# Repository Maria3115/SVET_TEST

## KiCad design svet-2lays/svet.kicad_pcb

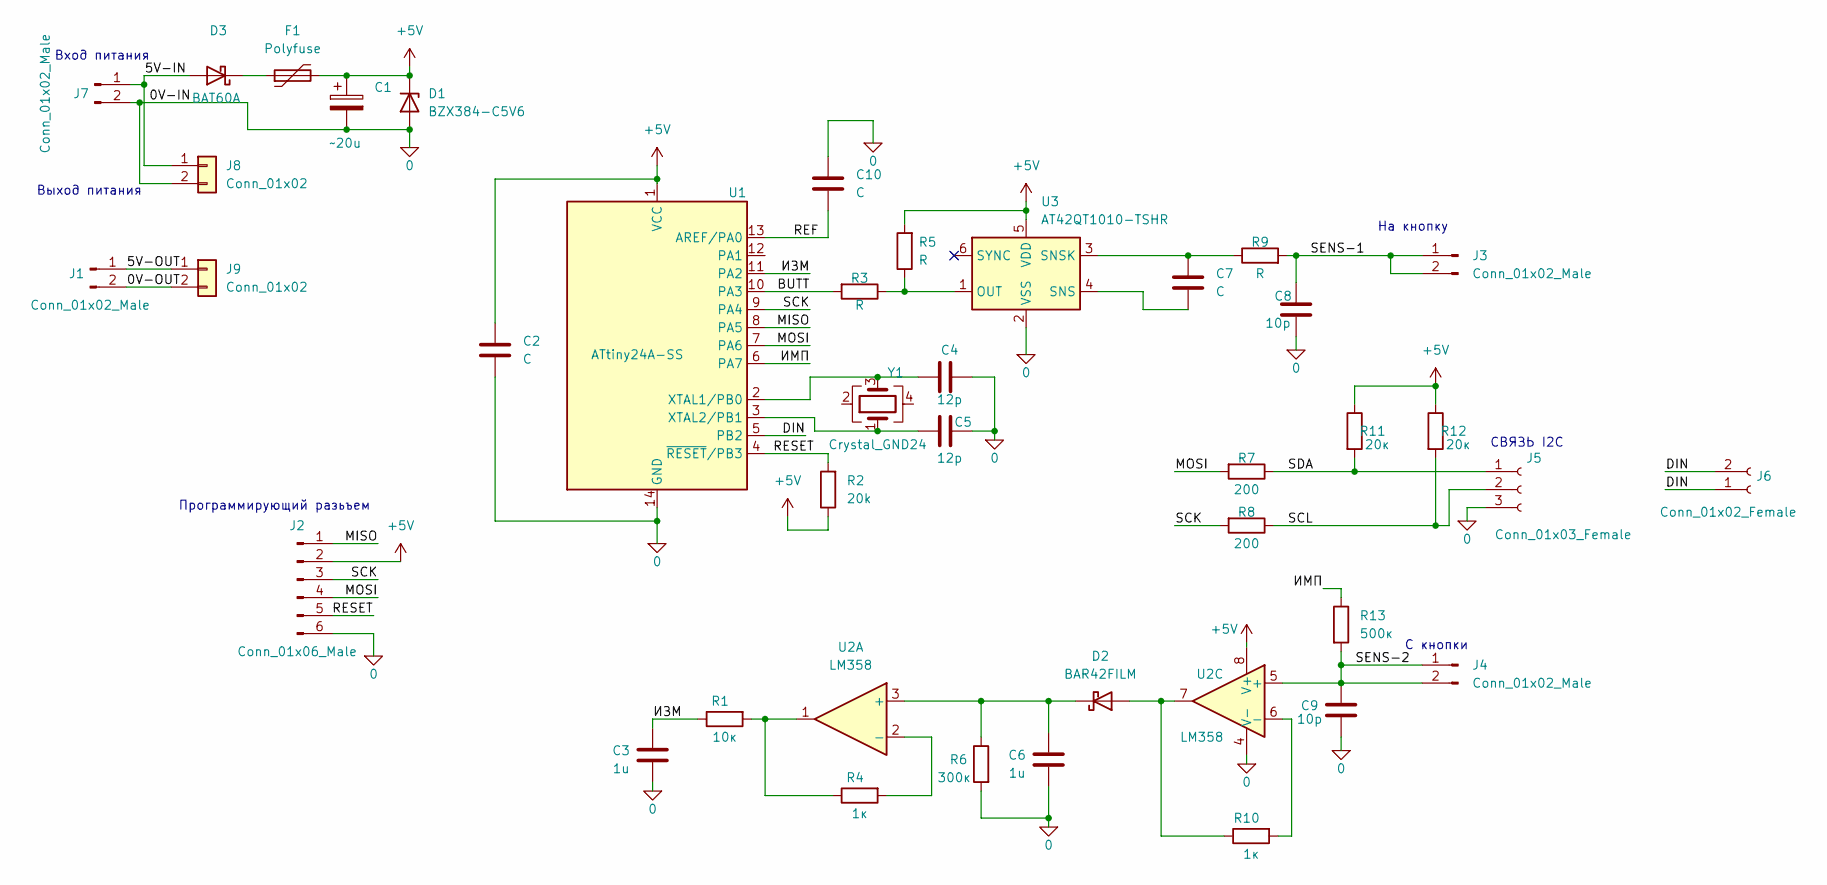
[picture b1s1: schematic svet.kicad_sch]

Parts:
C1: ~20u; CP_EIA-3216-18_Kemet-A_Pad1.58x1.35mm_HandSolder
C2, C7, C10: C; C_0603_1608Metric_Pad1.08x0.95mm_HandSolder
C3, C6: 1u; C_0603_1608Metric_Pad1.08x0.95mm_HandSolder
C4, C5: 12p; C_0603_1608Metric_Pad1.08x0.95mm_HandSolder
C8, C9: 10p; C_0603_1608Metric_Pad1.08x0.95mm_HandSolder
D1: BZX384-C5V6; D_SOD-323
D2: BAR42FILM; SOT-23
D3: BAT60A; D_SOD-323
F1: Polyfuse; R_0805_2012Metric
J1, J7: Conn_01x02_Male; SolderWire-2sqmm_1x02_P7.8mm_D2mm_OD3.9mm
J2: Conn_01x06_Male; PinHeader_2x03_P1.27mm_Horizontal
J3, J4: Conn_01x02_Male; PinHeader_1x02_P1.27mm_Horizontal
J5: Conn_01x03_Female; PinHeader_1x03_P1.27mm_Horizontal
J6: Conn_01x02_Female; SolderWire-0.5sqmm_1x02_P4.6mm_D0.9mm_OD2.1mm
J8, J9: Conn_01x02; Контактная площадка х2
R1: 10к; R_0603_1608Metric_Pad0.98x0.95mm_HandSolder
R2: 20k; R_0603_1608Metric_Pad0.98x0.95mm_HandSolder
R3, R5, R9: R; R_0603_1608Metric_Pad0.98x0.95mm_HandSolder
R4, R10: 1к; R_0603_1608Metric_Pad0.98x0.95mm_HandSolder
R6: 300к; R_0603_1608Metric_Pad0.98x0.95mm_HandSolder
R7, R8: 200; R_0603_1608Metric_Pad0.98x0.95mm_HandSolder
R11, R12: 20к; R_0603_1608Metric_Pad0.98x0.95mm_HandSolder
R13: 500к; R_0603_1608Metric_Pad0.98x0.95mm_HandSolder
U1: ATtiny24A-SS; SOIC-14_3.9x8.7mm_P1.27mm
U2: LM358; SOIC-8-1EP_3.9x4.9mm_P1.27mm_EP2.29x3mm
U3: AT42QT1010-TSHR; SOT-23-6
Y1: Crystal_GND24; Crystal_SMD_EuroQuartz_MT-4Pin_3.2x2.5mm_HandSoldering

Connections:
0: C1.2, C2.2, C3.1, C4.2, C5.2, C6.1, C8.2, C9.1, C10.1, D1.2 (A), J2.6, J5.3, J7.2, J8.2, R6.2, U1.14 (GND), U2.4 (V-), U3.2 (VSS)
+5V: C1.1, C2.1, D1.1 (K), F1.2, J2.2, R2.1, R5.2, R11.1, R12.1, U1.1 (VCC), U2.8 (V+), U3.5 (VDD)
/0V-OUT: J1.2, J9.2
/5V-IN: D3.2 (A), J7.1, J8.1
/5V-OUT: J1.1, J9.1
/BUTT: R3.2, U1.10 (PA3)
/DIN: J6.1, J6.2, U1.5 (PB2)
/MISO: J2.1, U1.8 (PA5)
/MOSI: J2.4, R7.2, U1.7 (PA6)
/REF: C10.2, U1.13 (AREF/PA0)
/RESET: J2.5, R2.2, U1.4 (~RESET/PB3)
/SCK: J2.3, R8.2, U1.9 (PA4)
/SCL: J5.2, R8.1, R12.2
/SDA: J5.1, R7.1, R11.2
/SENS-1: C8.1, J3.1, J3.2, R9.2
/SENS-2: C9.2, J4.1, J4.2, R13.2, U2.5 (+)
/ИЗМ: C3.2, R1.1, U1.11 (PA2)
/ИМП: R13.1, U1.6 (PA7)
unnamed: C4.1, U1.2 (XTAL1/PB0), Y1.3
unnamed: C5.1, U1.3 (XTAL2/PB1), Y1.1
unnamed: C6.2, D2.3 (K), R6.1, U2.3 (+)
unnamed: C7.1, R9.1, U3.3 (SNSK)
unnamed: C7.2, U3.4 (SNS)
unnamed: D2.1 (A), R10.1, U2.7
unnamed: D3.1 (K), F1.1
unnamed: R1.2, R4.1, U2.1
unnamed: R3.1, R5.1, U3.1 (OUT)
unnamed: R4.2, U2.2 (-)
unnamed: R10.2, U2.6 (-)

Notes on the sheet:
C кнопки
СВЯЗЬ I2C
Вход питания
Выход питания
Программирующий разьъем
На кнопку

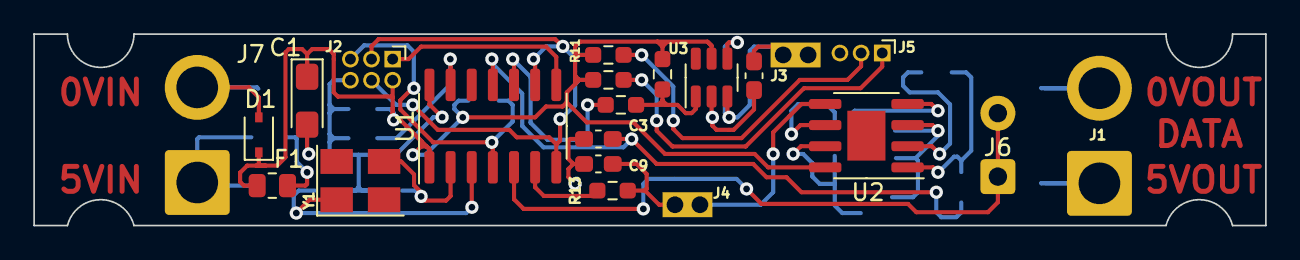
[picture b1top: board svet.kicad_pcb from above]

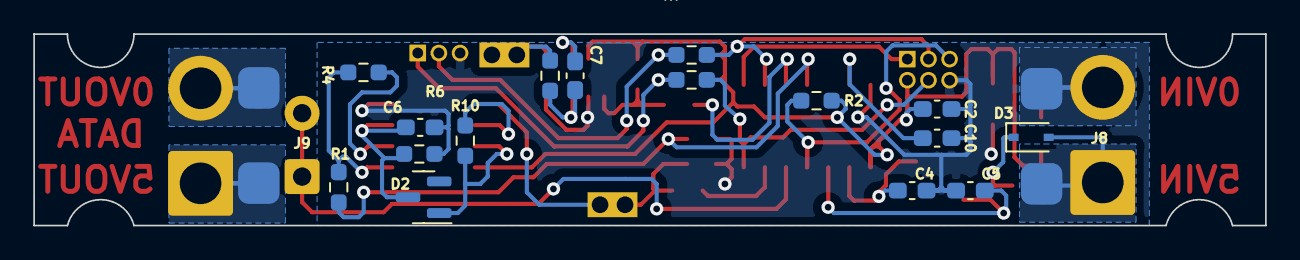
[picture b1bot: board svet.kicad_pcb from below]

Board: 4 copper layers, 74.0 x 11.5 mm, 40 parts (18 on the bottom side), 29 nets.

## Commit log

2022-01-24 проект и прога
